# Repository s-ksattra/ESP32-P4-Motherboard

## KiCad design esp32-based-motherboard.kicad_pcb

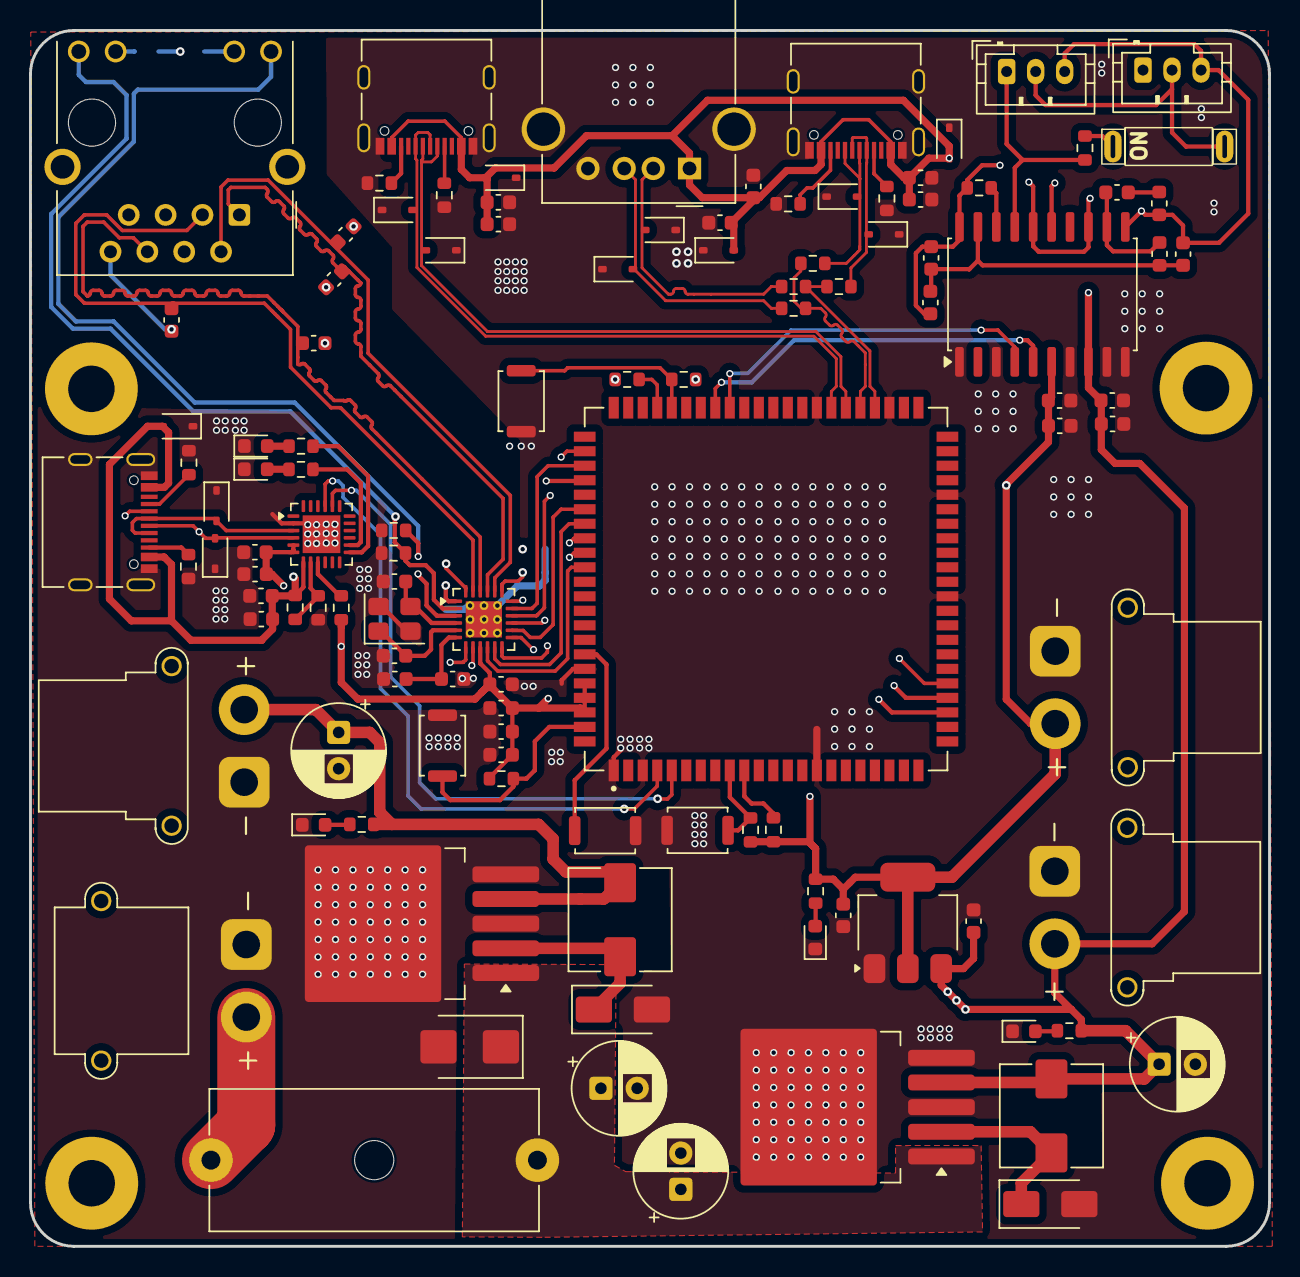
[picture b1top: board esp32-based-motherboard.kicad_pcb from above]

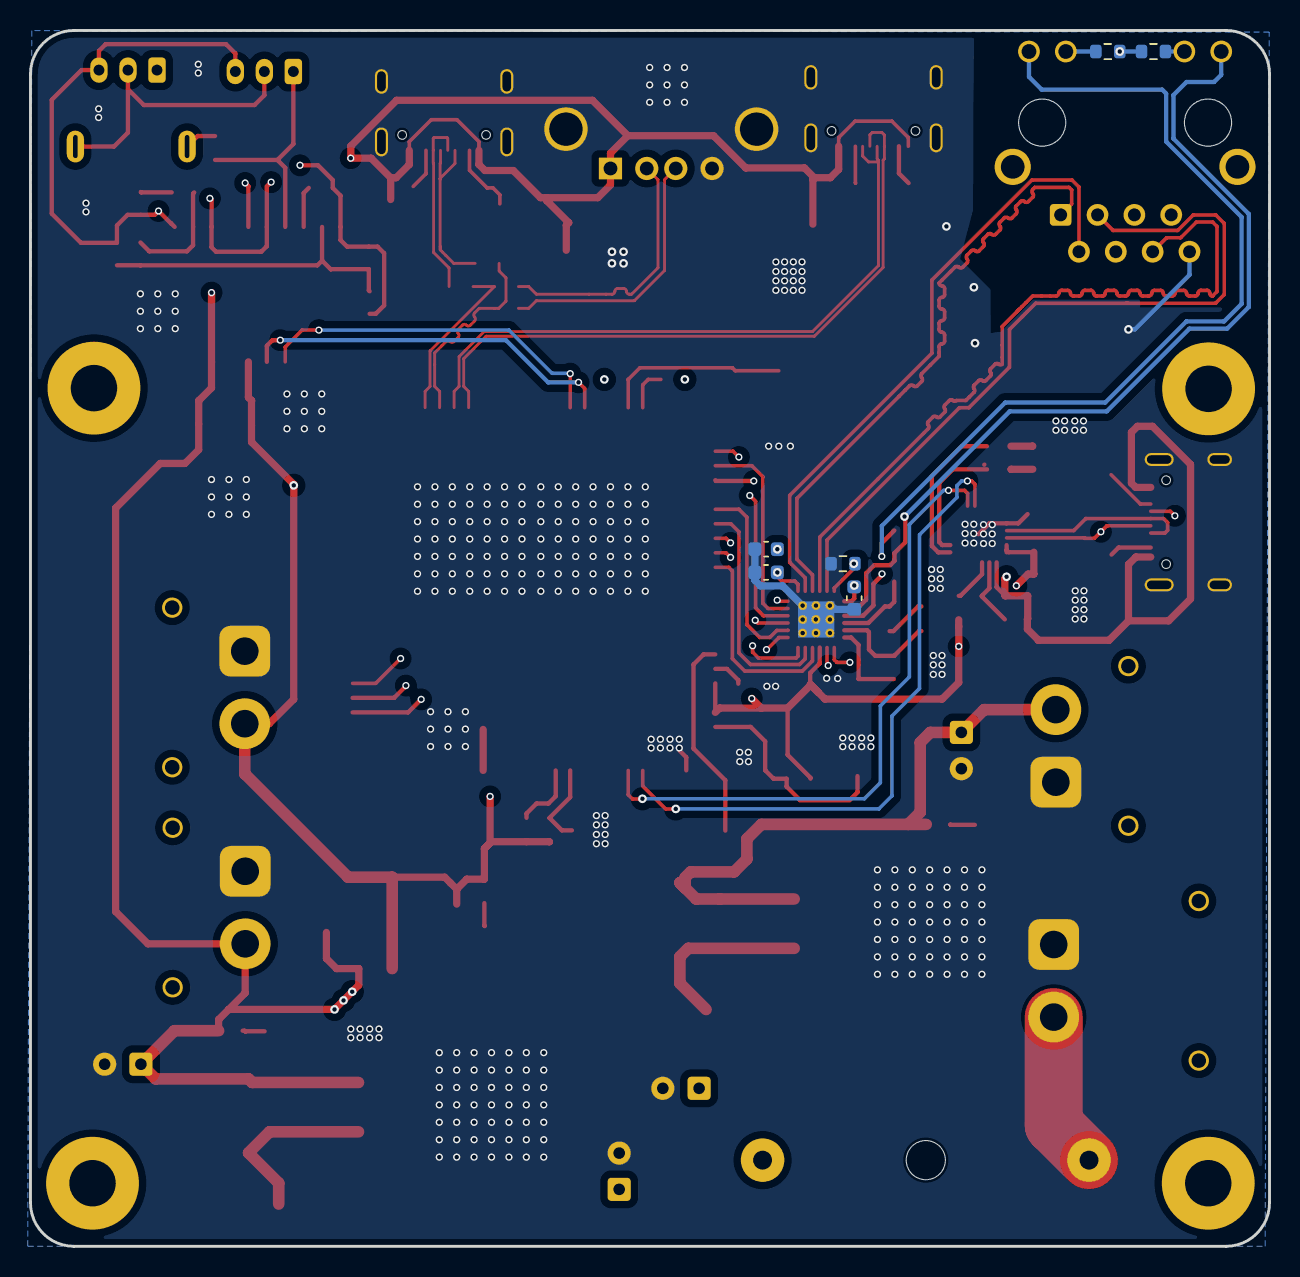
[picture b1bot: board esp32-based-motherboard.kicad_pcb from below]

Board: 4 copper layers, 85.4 x 83.8 mm, 122 parts (6 on the bottom side), 74 nets.

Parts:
C1, C3, C5, C9, C13, C15, C20, C30, C31, C32, C34: 10uF; C_0603_1608Metric
C2, C4, C6, C7, C8, C11, C12, C14, C21, C22, C23, C33, C35: 0.1uF; C_0603_1608Metric
C10: 0.01uF; C_0603_1608Metric
C16: 10nF; C_0603_1608Metric
C17: 100nF; C_0603_1608Metric
C18, C19, C36, C37, C38, C39: 12pF; C_0603_1608Metric
C24: 470pF; C_0603_1608Metric
C25: 1uF; C_0603_1608Metric
C26, C28: 470UF; CP_Radial_D6.3mm_P2.50mm
C27, C29: 47UF; CP_Radial_D6.3mm_P2.50mm
D1, D2, D3, D5, D7, D8, D9, D10, D11, D12: SD05C-01F; D_SOD-323
D4, D6: ESD7951ST5G; D_SOD-323
D13, D14, D17, D19, D20: LED; LED_0603_1608Metric
D15: SS56; D_SMB
D16, D18: 1N5822; D_SMA
F1: Fuse; Fuseholder_Cylinder-5x20mm_Schurter_0031_8201_Horizontal_Op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
FB1, FB2: FerriteBead; L_0603_1608Metric
H1, H2, H3, H4: MountingHole_Pad; MountingHole_3.2mm_M3_Pad
J1: USB_A; USB_A_Molex_67643_Horizontal
J2, J3, J4: USB_C_Receptacle_USB2.0_16P; USB_C_Receptacle_Palconn_UTC16-G
J5, J6: Conn_01x03_Pin; JST_PH_B3B-PH-K_1x03_P2.00mm_Vertical
J7: RJ45_Hanrun_HR911105A_Horizontal
J8: Conn_01x02_Pin; AMASS_XT30PW-M_1x02_P2.50mm_Horizontal
J9, J10, J11: Conn_01x02_Pin; AMASS_XT30PW-F_1x02_P2.50mm_Horizontal
L1, L2: 47uH; L_Wuerth_HCI-7030
R1, R2, R3, R4, R9, R10: 5.1k; R_0603_1608Metric
R5, R6, R7, R8, R20: 0; R_0603_1608Metric
R11, R16, R17, R18, R19, R21, R23, R25: 10k; R_0603_1608Metric
R12: 47k; R_0603_1608Metric
R13, R14, R15, R29: 1k; R_0603_1608Metric
R22: 120; R_0603_1608Metric
R24: 12.1k (1%); R_0603_1608Metric
R26, R27, R30: 500; R_0603_1608Metric
R28: 2k; R_0603_1608Metric
SW1, SW2, SW3, SW4: SW_Push; SW_Push_SPST_NO_Alps_SKRK
SW5: SW_SPST; DSIC01LHGET_C54957
U1: ESP32-P4_MODULE
U2: CP2102N-Axx-xQFN24; QFN-24-1EP_4x4mm_P0.5mm_EP2.6x2.6mm
U3: ADM3053; SOIC-20W_7.5x12.8mm_P1.27mm
U4: LAN8720A; VQFN-24-1EP_4x4mm_P0.5mm_EP2.5x2.5mm_ThermalVias
U5: LM2596S-12; TO-263-5_TabPin3
U6: LM2596S-5; TO-263-5_TabPin3
U7: AMS1117-3.3; SOT-223-3_TabPin2
Y1: 25MHz; Crystal_SMD_3225-4Pin_3.2x2.5mm

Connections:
+3.3V: C3.2, C4.2, C7.2, C8.2, C9.2, C10.2, C11.2, C20.2, C21.2, C22.2, C23.2, C30.1, J11.2, R13.2, R16.1, R17.1, R18.1, R19.1, R21.1, R30.1, U1.84 (VBAT), U1.85 (ESP_3V3), U1.86 (ESP_3V3), U2.5 (VIO), U2.6 (VDD), U3.6 (VIO), U4.1 (VDD2A), U4.9 (VDDIO), U4.19 (VDD1A), U7.2 (VO)
+5V: C1.1, C2.1, C5.2, C6.2, C12.1, C13.1, C29.1, C31.1, C32.1, C33.1, C34.1, C35.1, D3.2 (A2), D8.2 (A2), D9.2 (A2), D12.2 (A2), J1.1 (VBUS), J2.A4 (VBUS), J2.A9 (VBUS), J2.B4 (VBUS), J2.B9 (VBUS), J3.A4 (VBUS), J3.A9 (VBUS), J3.B4 (VBUS), J3.B9 (VBUS), J4.A4 (VBUS), J4.A9 (VBUS), J4.B4 (VBUS), J4.B9 (VBUS), J10.2, L2.2, R11.2, R29.1, U2.7 (VREGIN), U3.8 (VCC), U6.4 (FB), U7.3 (VI)
+12V: C27.1, J9.2, L1.2, R28.1, U5.4 (FB)
/USB_A_N: D1.2 (A2), J1.2 (D-), R6.1
/USB_A_P: D2.2 (A2), J1.3 (D+), R5.1
/USB_C_N: D6.2 (A2), J2.A7 (D-), J2.B7 (D-), R7.1
/USB_C_P: D4.2 (A2), J2.A6 (D+), J2.B6 (D+), R8.1
/power_system/Vcc: C26.1, C28.1, D15.1 (K), F1.2, U5.1 (VIN), U6.1 (VIN)
BOOT: R17.2, SW2.2, U1.62 (GPIO35/BOOT)
BOOT_EN: R19.2, U1.63 (GPIO36/BOOT_EN)
C6_BOOT: R18.2, SW3.2, U1.9 (C6_IO9/BOOT)
C6_BOOT_EN: R21.2, U1.10 (C6_IO8/BOOT_EN)
C6_EN: SW4.2, U1.82 (GPIO54)
C6_UART_RX: U1.4 (C6_U0RXD), U2.21 (TXD)
C6_UART_TX: U1.5 (C6_U0TXD), U2.20 (RXD)
CAN_H: J5.1, J6.1, R22.2, U3.17 (CANH)
CAN_L: J5.2, J6.2, SW5.2 (B), U3.15 (CANL)
CAN_RX: U1.58 (GPIO31), U3.4 (RXD)
CAN_TX: U1.59 (GPIO32), U3.5 (TXD)
D+: D10.2 (A2), J4.A6 (D+), J4.B6 (D+), U2.3 (D+)
D-: D11.2 (A2), J4.A7 (D-), J4.B7 (D-), U2.4 (D-)
EN: R16.2, SW1.2, U1.87 (ESP_EN)
ETH_RD+: C39.2, J7.3 (RD+), U4.23 (RXP)
ETH_RD-: C38.2, J7.6 (RD-), U4.22 (RXN)
ETH_TD+: C36.2, J7.1 (TD+), U4.21 (TXP)
ETH_TD-: C37.2, J7.2 (TD-), U4.20 (TXN)
GND: C1.2, C2.2, C3.1, C4.1, C5.1, C6.1, C7.1, C8.1, C9.1, C10.1, C11.1, C12.2, C13.2, C18.1, C19.1, C20.1, C21.1, C22.1, C23.1, C24.2, C25.2, C26.2, C27.2, C28.2, C29.2, C30.2, C31.2, C32.2, C33.2, C34.2, C35.2, C36.1, C37.1, C38.1, C39.1, D1.1 (A1), D2.1 (A1), D3.1 (A1), D4.1 (A1), D5.1 (A1), D6.1 (A1), D7.1 (A1), D8.1 (A1), D9.1 (A1), D10.1 (A1), D11.1 (A1), D12.1 (A1), D13.1 (K), D14.1 (K), D15.2 (A), D16.2 (A), D17.1 (K), D18.2 (A), D19.1 (K), D20.1 (K), J1.4 (GND), J1.5 (Shield), J2.A1 (GND), J2.A12 (GND), J2.B1 (GND), J2.B12 (GND), J2.S1 (SHIELD), J3.A1 (GND), J3.A12 (GND), J3.B1 (GND), J3.B12 (GND), J3.S1 (SHIELD), J4.A1 (GND), J4.A12 (GND), J4.B1 (GND), J4.B12 (GND), J4.S1 (SHIELD), J7.8, J8.1, J9.1, J10.1, J11.1, R1.2, R2.2, R3.2, R4.2, R9.2, R10.2, R12.1, R23.2, R24.2, R25.2, R26.1, R27.1, SW1.1, SW2.1, SW3.1, SW4.1, U1.1 (GND), U1.3 (GND), U1.15 (GND), U1.33 (GND), U1.40 (GND), U1.47 (GND), U1.52 (GND), U1.83 (GND), U2.2 (GND), U2.25 (GND), U3.1 (GND1), U3.3 (GND1), U3.7 (GND1), U3.9 (GND1), U3.10 (GND1), U4.25 (VSS), U5.3 (GND), U5.5 (~ON/OFF), U6.3 (GND), U6.5 (~ON/OFF), U7.1 (GND), Y1.2 (G), Y1.4 (G)
GNDREF: C15.1, C16.1, C17.1, FB1.2, J5.3, J6.3, R20.1, U3.11 (GND2), U3.13 (GND2), U3.16 (GND2), U3.20 (GND2)
unnamed: C14.1, FB1.1
unnamed: D13.2 (A), R14.1
unnamed: D14.2 (A), R15.1
unnamed: D16.1 (K), L1.1, U5.2 (OUT)
unnamed: D17.2 (A), R28.2
unnamed: D18.1 (K), L2.1, U6.2 (OUT)
unnamed: D19.2 (A), R29.2
unnamed: D20.2 (A), R30.2
unnamed: J2.A5 (CC1), R1.1
unnamed: J2.B5 (CC2), R2.1
unnamed: J3.A5 (CC1), R3.1
unnamed: J3.B5 (CC2), R4.1
unnamed: J4.A5 (CC1), R9.1
unnamed: J4.B5 (CC2), R10.1
unnamed: J7.10, R27.2
unnamed: J7.11, R26.2
unnamed: F1.1, J8.2
unnamed: R22.1, SW5.1 (A)
unnamed: R11.1, R12.2, U2.8 (VBUS)
unnamed: R13.1, U2.9 (~RST)
unnamed: R15.2, U2.13 (~RXT/GPIO.1)
unnamed: R14.2, U2.14 (~TXT/GPIO.0)
unnamed: R20.2, U3.18 (RS)
unnamed: C15.2, C16.2, C17.2, FB2.1, U3.19 (VISOIN)
unnamed: C14.2, FB2.2, U3.12 (VISOOUT)
unnamed: R24.1, U4.24 (RBIAS)
unnamed: C24.1, C25.1, U4.6 (VDDCR)
PHY_LED1: J7.9, R25.1, U4.3 (LED1/REGOFF)
PHY_LED2: J7.12, R23.1, U4.2 (LED2/~INTSEL)
PHY_MDC: U1.25 (GPIO10), U4.13 (MDC)
PHY_MDIO: U1.26 (GPIO11), U4.12 (MDIO)
PHY_Reset: U1.27 (GPIO12), U4.15 (~RST)
RMII_CLK: U1.72 (GPIO44), U4.14 (~INT/REFCLKO)
RMII_CRSDV: U1.73 (GPIO45), U4.11 (CRS_DV/MODE2)
RMII_RXD0: U1.74 (GPIO46), U4.8 (RXD0/MODE0)
RMII_RXD1: U1.75 (GPIO47), U4.7 (RXD1/MODE1)
RMII_RXER: U1.76 (GPIO48), U4.10 (RXER/PHYAD0)
RMII_TXD0: U1.69 (GPIO41), U4.17 (TXD0)
RMII_TXD1: U1.70 (GPIO42), U4.18 (TXD1)
RMII_TXEN: U1.68 (GPIO40), U4.16 (TXEN)
USB1P1_N: D7.2 (A2), J3.A7 (D-), J3.B7 (D-), U1.50 (GPIO24/USB1P1_N0)
USB1P1_P: D5.2 (A2), J3.A6 (D+), J3.B6 (D+), U1.51 (GPIO25/USB1P1_P0)
USBHS_N: R6.2, R7.2, U1.48 (USB_DM)
USBHS_P: R5.2, R8.2, U1.49 (USB_DP)
XTAL1: C18.2, U4.5 (XTAL1/CLKIN), Y1.1
XTAL2: C19.2, U4.4 (XTAL2), Y1.3

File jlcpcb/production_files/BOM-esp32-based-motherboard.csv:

Comment,Designator,Footprint,LCSC,Quantity
LAN8720A,U4,VQFN-24-1EP_4x4mm_P0.5mm_EP2.5x2.5mm_ThermalVias,,1
ESP32-P4_MODULE,U1,ESP32-P4_MODULE,,1
500,R26,R_0603_1608Metric,,1
12pF,C38,C_0603_1608Metric,,1
0.1uF,C22,C_0603_1608Metric,,1
47UF,C27,CP_Radial_D6.3mm_P2.50mm,,1
10k,R21,R_0603_1608Metric,,1
10uF,C34,C_0603_1608Metric,,1
ESD7951ST5G,D4,D_SOD-323,,1
SS56,D15,D_SMB,,1
5.1k,R3,R_0603_1608Metric,,1
0,R5,R_0603_1608Metric,,1
Conn_01x02_Pin,J8,AMASS_XT30PW-M_1x02_P2.50mm_Horizontal,,1
SD05C-01F,D10,D_SOD-323,,1
LED,D20,LED_0603_1608Metric,,1
47uH,L2,L_Wuerth_HCI-7030,,1
SD05C-01F,D7,D_SOD-323,,1
47uH,L1,L_Wuerth_HCI-7030,,1
100nF,C17,C_0603_1608Metric,,1
10k,R25,R_0603_1608Metric,,1
500,R30,R_0603_1608Metric,,1
120,R22,R_0603_1608Metric,,1
47UF,C29,CP_Radial_D6.3mm_P2.50mm,,1
0.1uF,C6,C_0603_1608Metric,,1
USB_A,J1,USB_A_Molex_67643_Horizontal,,1
RJ45_Hanrun_HR911105A_Horizontal,J7,RJ45_Hanrun_HR911105A_Horizontal,,1
1N5822,D16,D_SMA,,1
0.1uF,C33,C_0603_1608Metric,,1
0.01uF,C10,C_0603_1608Metric,,1
SW_Push,SW2,SW_Push_SPST_NO_Alps_SKRK,,1
0,R8,R_0603_1608Metric,,1
1k,R14,R_0603_1608Metric,,1
12pF,C39,C_0603_1608Metric,,1
LED,D14,LED_0603_1608Metric,,1
12pF,C19,C_0603_1608Metric,,1
FerriteBead,FB2,L_0603_1608Metric,,1
10uF,C30,C_0603_1608Metric,,1
0.1uF,C35,C_0603_1608Metric,,1
12pF,C37,C_0603_1608Metric,,1
USB_C_Receptacle_USB2.0_16P,J3,USB_C_Receptacle_Palconn_UTC16-G,,1
1k,R15,R_0603_1608Metric,,1
10k,R19,R_0603_1608Metric,,1
10uF,C13,C_0603_1608Metric,,1
2k,R28,R_0603_1608Metric,,1
SD05C-01F,D2,D_SOD-323,,1
470pF,C24,C_0603_1608Metric,,1
5.1k,R10,R_0603_1608Metric,,1
0.1uF,C11,C_0603_1608Metric,,1
LED,D19,LED_0603_1608Metric,,1
0.1uF,C4,C_0603_1608Metric,,1
Conn_01x03_Pin,J6,JST_PH_B3B-PH-K_1x03_P2.00mm_Vertical,,1
Fuse,F1,Fuseholder_Cylinder-5x20mm_Schurter_0031_8201_Horizontal_Open,,1
SD05C-01F,D1,D_SOD-323,,1
Conn_01x02_Pin,J10,AMASS_XT30PW-F_1x02_P2.50mm_Horizontal,,1
10nF,C16,C_0603_1608Metric,,1
10uF,C5,C_0603_1608Metric,,1
1uF,C25,C_0603_1608Metric,,1
Conn_01x02_Pin,J9,AMASS_XT30PW-F_1x02_P2.50mm_Horizontal,,1
SD05C-01F,D5,D_SOD-323,,1
10uF,C32,C_0603_1608Metric,,1
47k,R12,R_0603_1608Metric,,1
SD05C-01F,D9,D_SOD-323,,1
0.1uF,C14,C_0603_1608Metric,,1
5.1k,R4,R_0603_1608Metric,,1
1N5822,D18,D_SMA,,1
LED,D17,LED_0603_1608Metric,,1
10k,R11,R_0603_1608Metric,,1
5.1k,R2,R_0603_1608Metric,,1
10uF,C9,C_0603_1608Metric,,1
0.1uF,C8,C_0603_1608Metric,,1
SW_Push,SW1,SW_Push_SPST_NO_Alps_SKRK,,1
SD05C-01F,D11,D_SOD-323,,1
Conn_01x03_Pin,J5,JST_PH_B3B-PH-K_1x03_P2.00mm_Vertical,,1
0,R7,R_0603_1608Metric,,1
10k,R23,R_0603_1608Metric,,1
AMS1117-3.3,U7,SOT-223-3_TabPin2,,1
SW_SPST,SW5,DSIC01LHGET_C54957,,1
0,R6,R_0603_1608Metric,,1
CP2102N-Axx-xQFN24,U2,QFN-24-1EP_4x4mm_P0.5mm_EP2.6x2.6mm,,1
500,R27,R_0603_1608Metric,,1
470UF,C28,CP_Radial_D6.3mm_P2.50mm,,1
FerriteBead,FB1,L_0603_1608Metric,,1
LED,D13,LED_0603_1608Metric,,1
10k,R18,R_0603_1608Metric,,1
LM2596S-12,U5,TO-263-5_TabPin3,,1
10uF,C31,C_0603_1608Metric,,1
470UF,C26,CP_Radial_D6.3mm_P2.50mm,,1
5.1k,R9,R_0603_1608Metric,,1
USB_C_Receptacle_USB2.0_16P,J2,USB_C_Receptacle_Palconn_UTC16-G,,1
10uF,C15,C_0603_1608Metric,,1
10uF,C1,C_0603_1608Metric,,1
SD05C-01F,D12,D_SOD-323,,1
SD05C-01F,D8,D_SOD-323,,1
SD05C-01F,D3,D_SOD-323,,1
0.1uF,C2,C_0603_1608Metric,,1
ADM3053,U3,SOIC-20W_7.5x12.8mm_P1.27mm,,1
5.1k,R1,R_0603_1608Metric,,1
USB_C_Receptacle_USB2.0_16P,J4,USB_C_Receptacle_Palconn_UTC16-G,,1
SW_Push,SW4,SW_Push_SPST_NO_Alps_SKRK,,1
1k,R29,R_0603_1608Metric,,1
LM2596S-5,U6,TO-263-5_TabPin3,,1
12pF,C36,C_0603_1608Metric,,1
25MHz,Y1,Crystal_SMD_3225-4Pin_3.2x2.5mm,,1
ESD7951ST5G,D6,D_SOD-323,,1
10k,R16,R_0603_1608Metric,,1
0,R20,R_0603_1608Metric,,1
Conn_01x02_Pin,J11,AMASS_XT30PW-F_1x02_P2.50mm_Horizontal,,1
SW_Push,SW3,SW_Push_SPST_NO_Alps_SKRK,,1
10k,R17,R_0603_1608Metric,,1
12pF,C18,C_0603_1608Metric,,1
0.1uF,C12,C_0603_1608Metric,,1
1k,R13,R_0603_1608Metric,,1
10uF,C3,C_0603_1608Metric,,1
0.1uF,C7,C_0603_1608Metric,,1
0.1uF,C21,C_0603_1608Metric,,1
0.1uF,C23,C_0603_1608Metric,,1
12.1k (1%),R24,R_0603_1608Metric,,1
10uF,C20,C_0603_1608Metric,,1
